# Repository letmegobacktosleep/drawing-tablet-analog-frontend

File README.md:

# Diode-Detector based Analog Frontend

### Warning: Please read cl 6 of the license

This hardware has not been tested (yet) due to a lack of funds.<br>
Sponsor me if you want it tested (つ✧ω✧)つ

## License

The hardware design is released under the CERN Open Source Hardware License strongly-reciprocal variant, [CERN-OHL-S](https://ohwr.org/cern_ohl_s_v2.txt). A copy of the license is provided in the source repository. Additionally, a user guide of the license is provided on [ohwr.org](https://ohwr.org).

The schematic is largely based on the [Patchouli Project](https://gitlab.com/yukidama/patchouli), the PCB layout is entirely original.

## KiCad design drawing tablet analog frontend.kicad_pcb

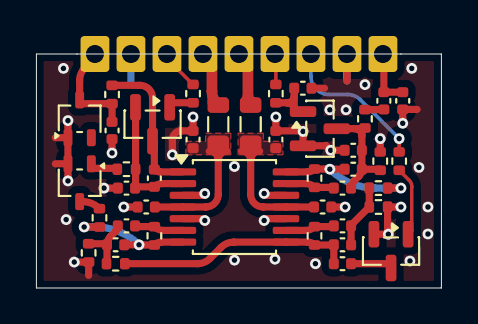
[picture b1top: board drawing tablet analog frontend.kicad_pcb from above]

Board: 2 copper layers, 22.5 x 13.0 mm, 42 parts (0 on the bottom side), 28 nets.

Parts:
C1, C4: 1n; C_0402_1005Metric
C2: 10n; C_0402_1005Metric
C3, C9, C16: 470p; C_0402_1005Metric
C5, C6, C7, C8, C10, C11: 120p; C_0402_1005Metric
C12: 33p; C_0402_1005Metric
C13: 220p; C_0402_1005Metric
C14, C17: 1u; C_0402_1005Metric
C15, C18: 100n; C_0402_1005Metric
D1, D2: BAT54SW; SOT-323_SC-70
FB1, FB2: 100Ω @ 100MHz; L_0805_2012Metric
J1: Conn_01x09; castellated_edge_P2.00mm_01x09
Q1, Q2, Q3: AO3400A; SOT-23
R1: 470; R_0402_1005Metric
R2, R8: 1k; R_0402_1005Metric
R3, R6, R10, R14: 10k; R_0402_1005Metric
R4, R7, R11: 12k; R_0402_1005Metric
R5: 510; R_0402_1005Metric
R9: 220; R_0402_1005Metric
R12, R15: 100; R_0402_1005Metric
R13: 15k; R_0402_1005Metric
U1: COS8054TR; TSSOP-14_4.4x5mm_P0.65mm

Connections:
+2.5VA: FB1.1, J1.4
/integrator_5/ABUS: C1.1, C2.1, J1.9
/integrator_5/DISCHARGE: J1.3, R14.2
/integrator_5/INHIBIT: J1.6, R2.1
/integrator_5/INTEGRAL: C16.1, D2.3 (COM), J1.1, R15.2
/integrator_5/REDUCE: J1.7, R8.1
GND: C1.2, C3.2, C4.2, C12.2, C14.2, C15.2, C16.2, C17.1, C18.1, D1.2 (K), D2.1 (A), J1.2, J1.8, Q1.2 (S), Q2.2 (S), R3.2, R6.2, R10.2, U1.3 (+), U1.5 (+), U1.10 (+), U1.12 (+)
unnamed: C2.2, R1.1
unnamed: C5.2, R4.1, R5.1, U1.14
unnamed: C7.1, C8.1, R5.2, R6.1
unnamed: C7.2, C9.1, R7.1, R9.1, U1.8
unnamed: C10.1, C11.1, R9.2, R10.1
unnamed: C10.2, R11.1, R12.1, U1.7
unnamed: D1.1 (A), R13.1
unnamed: D1.3 (COM), R12.2
unnamed: C3.1, C5.1, C6.1, Q1.3 (D), R1.2, R3.1
unnamed: C4.1, Q1.1 (G), R2.2
unnamed: C9.2, Q2.3 (D)
unnamed: Q2.1 (G), R8.2
unnamed: C13.2, Q3.3 (D), R15.1, U1.1
unnamed: Q3.1 (G), R14.1
unnamed: C12.1, C13.1, Q3.2 (S), R13.2, U1.2 (-)
unnamed: C11.2, R11.2, U1.6 (-)
unnamed: C8.2, R7.2, U1.9 (-)
unnamed: C6.2, R4.2, U1.13 (-)
unnamed: C14.1, C15.1, FB1.2, U1.4 (V+)
unnamed: C17.2, C18.2, FB2.2, U1.11 (V-)
VEE: FB2.1, J1.5

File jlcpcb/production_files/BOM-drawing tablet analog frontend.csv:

Comment,Designator,Footprint,LCSC,Quantity
100,"R12,R15",R_0402_1005Metric,C25076,2
100n,"C15,C18",C_0402_1005Metric,C1525,2
100Ω @ 100MHz,"FB1,FB2",L_0805_2012Metric,C1015,2
10k,"R10,R14,R3,R6",R_0402_1005Metric,C25744,4
10n,C2,C_0402_1005Metric,C15195,1
120p,"C10,C11,C5,C6,C7,C8",C_0402_1005Metric,C106996,6
12k,"R11,R4,R7",R_0402_1005Metric,C25752,3
15k,R13,R_0402_1005Metric,C25756,1
1k,"R2,R8",R_0402_1005Metric,C11702,2
1n,"C1,C4",C_0402_1005Metric,C1523,2
1u,"C14,C17",C_0402_1005Metric,C52923,2
220,R9,R_0402_1005Metric,C25091,1
220p,C13,C_0402_1005Metric,C1530,1
33p,,C_0402_1005Metric,C1562,0
470,R1,R_0402_1005Metric,C25117,1
470p,"C16,C3,C9",C_0402_1005Metric,C106259,3
510,R5,R_0402_1005Metric,C25123,1
AO3400A,"Q1,Q2,Q3",SOT-23,C20917,3
BAT54SW,"D1,D2",SOT-323_SC-70,C22466373,2
COS8054TR,U1,TSSOP-14_4.4x5mm_P0.65mm,C7463388,1
